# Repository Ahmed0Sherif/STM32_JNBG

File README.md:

# Intro
- This repository includes the schematics and PCB design of a double-layer STM32 development Board.
- The code name "JNBG" is in the honour of my group who helped and encouraged me in this project.
- The design is done on KiCAD 6.0
# Components List:
|Component|Description|Quantity| Was Used|
|----|-----|-------|-------|
|STM32f030f4p6|ARM® Cortex®-M0 48MHz FLASH 2.4V ~ 3.6V 32-Bit TSSOP-20 ST Microelectronics|1|Yes|
|AMS1117- 3V3| 3V3 LDO Linear Voltage Regulator  SOT-223-3|1|Yes|
|CH340C|IC Transceiver USB 2.0 2Mbps SOP-16|1|Yes|
|USBLC6-2SC6|ESD Protection TVS Unidirectional Dual Array SOT23-6|1|Yes|
|SMAJ5.0A|Unidirectional TVS 5.0V DO-214AC|1|Not Available|
|Crystal Oscillator|Crystal Oscillator 32MHz 3225|1|Yes|
|LEDs|Green and Red LEDs 0805|1* Green, 1*Red|Yes|
|Ferrite Bead|100Ω @ 100MHz 2.5A 1 100mΩ 0805|1|Yes|
|22uF Capacitor|SMD 22uF 0805|2|Replaced with 1205 Counterpart|
|4.7uF Capacitor|SMD 4.7uF 0603|2|Yes|
|1uF Capacitor|SMD 1uF 0603|2|Yes|
|100n Capacitor|SMD 100nF 0603|1|Yes|
|47nF Capacitor|SMD 47nF 0805|1|Yes|
|10nF Capacitor|SMD 10nF 0603|1|Yes|
|10pF Capacitor|SMD 10pF 0603|2|Yes|
|10k ohm Resistor|SMD 10k 0603|3|Yes|
|1k ohm Resistor|SMD 1k 0603|1|Yes|
|1k5 ohm Resistor|SMD 1k5 0603|3|Yes|
|Tactile Push Button|Micro Push button Switch 2P 3x4x2mm|1|Yes|
|PCB TH SPDT Toggle Switch| Through Hole SPDT Swithc pitch = 2.54mm |1|Yes|
|USB Port|SMD USB-B-Micro |1|Yes|
|Female Headers|TH Female Headers Vertical pitch = 2.54mm|13|Yes|
# Schematics:
## A-Power Module:

<br> - In this circuit, the AMS1117 is used to regulate 5V from USB to 3.3V, with a unidirectional TVS to protect against surges.

## B-USB Interface:

<br> - The board is provided with a USB-B Micro port, providing power and communication to the controller. 
<br> - The differential pair is connected to au nidirectional Dual TVS for ESD protection. Finally, the differentials are connected to a USB-to-TTL interface: CH340C. This variant was chosen because it can operate without an external crystal.
<br> - It is worth mentioning that until this time, this module has not been tested yet.

## C-Main Controller:

### a- Crystal Oscillator
- For calculting the value of capacitors, the following equation is used:
<br>   Capacitor Value =  ( Load Capaitance of Crystal [10pf] + Stray Capacitance of PCB [maximum estimate = 10pF] ) / 2
- Source: Phill's Lab Course on KiCAD 6.0
### b- Power:
- According to the datasheet of STM32f03x, it is recommeded to connect VDD pin to the shown capacitances.
- For more stable ADC performance, a ferrite bead is added to the VDDA connections.
### c- Interfacing:
- GPIO pins are connected to headers for easier interface, while taking speical signals into considerations (i.e. I2C pair)
- A SPDT switch is added to control the BOOT0 pin, and a RST button is added.
- For experimental purposes, extra pair of headers are added to power the STM32 directly, bypassing the regulator.

# PCB View:

# Final Result:

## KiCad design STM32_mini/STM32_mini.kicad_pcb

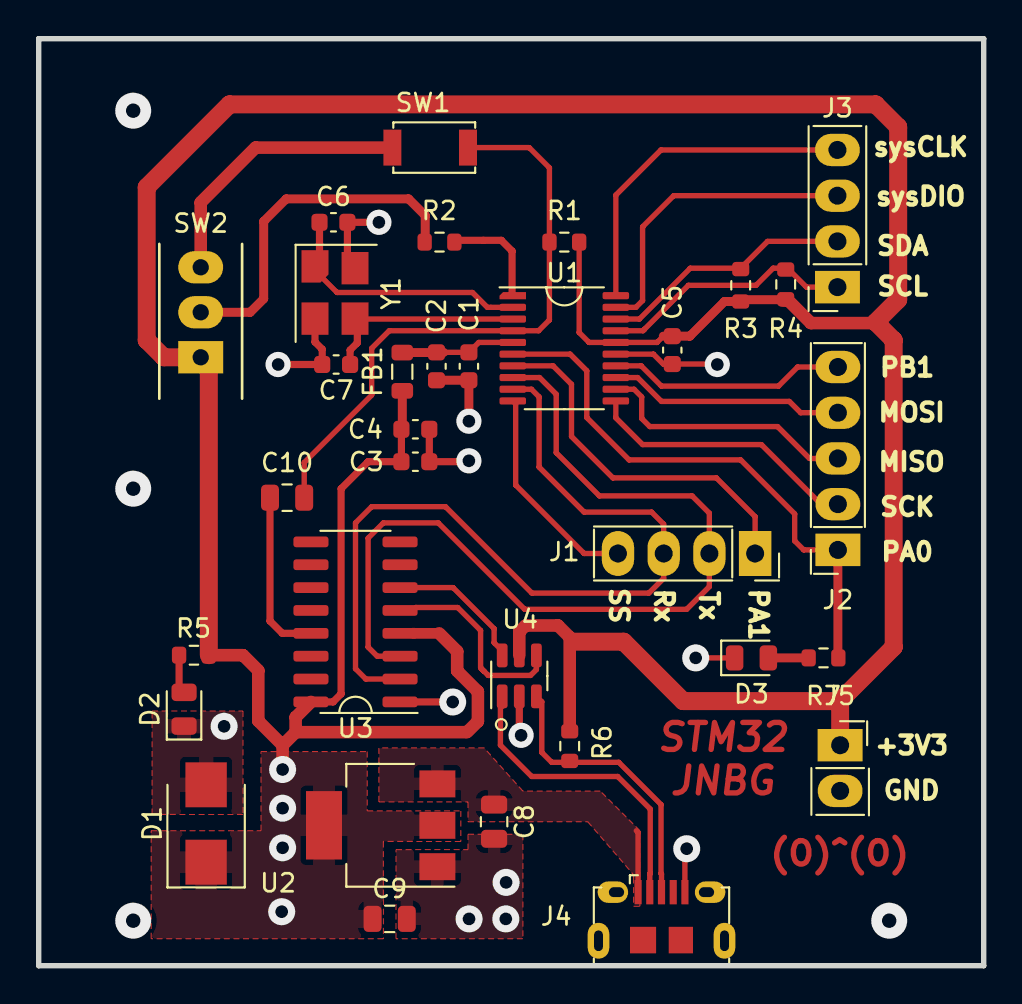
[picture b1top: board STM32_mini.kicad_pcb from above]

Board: 2 copper layers, 52.5 x 51.5 mm, 33 parts (0 on the bottom side), 29 nets.

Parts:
C1: 10n; C_0603_1608Metric
C2, C3: 1u; C_0603_1608Metric
C4: 4.7u; C_0603_1608Metric
C5: 100n; C_0603_1608Metric
C6, C7: 10p; C_0603_1608Metric
C8, C9: 22u; C_0805_2012Metric
C10: 47n; C_0805_2012Metric
D1: SMAJ5.0A; D_SMB
D2, D3: LED; LED_0805_2012Metric
FB1: 100R; L_0805_2012Metric
J1, J3: Conn_01x04_Female; PinSocket_1x04_P2.54mm_Vertical
J2: Conn_01x05_Female; PinSocket_1x05_P2.54mm_Vertical
J4: USB_B_Micro; USB_Micro-B_Amphenol_10118194_Horizontal
J5: Conn_01x02_Female; PinSocket_1x02_P2.54mm_Vertical
R1, R3, R4: 10k; R_0603_1608Metric
R2: 1k; R_0603_1608Metric
R5, R6, R7: 1k5; R_0603_1608Metric
SW1: SW_Push; SW_SPST_B3U-1000P
SW2: SW_SPDT; SW_CuK_OS102011MA1QN1_SPDT_Angled
U1: STM32F030F4Px; TSSOP-20_4.4x6.5mm_P0.65mm
U2: AMS1117-3.3; SOT-223-3_TabPin2
U3: CH340C; SOIC-16_3.9x9.9mm_P1.27mm
U4: USBLC6-2SC6; SOT-23-6
Y1: 32MHz; Crystal_SMD_3225-4Pin_3.2x2.5mm_HandSoldering

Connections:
+3.3VA: C1.1, C2.1, FB1.1, U1.5 (VDDA)
+3V3: C3.1, C4.1, C5.1, C9.1, D1.1 (A1), FB1.2, J5.1, R1.1, R3.1, R4.1, R5.1, R6.1, SW2.1 (A), U1.16 (VDD), U2.2 (VO), U3.4 (V3), U3.16 (VCC), U4.5 (VBUS)
/CH_D+: U3.5 (UD+), U4.4 (I/O2)
/CH_D-: U3.6 (UD-), U4.6 (I/O1)
/DTR: C10.2, U3.13 (~DTR)
/I2C_SCL: J3.1, R4.2, U1.17 (PA9)
/I2C_SDA: J3.2, R3.2, U1.18 (PA10)
/MISO: J2.3, U1.12 (PA6)
/MOSI: J2.4, U1.13 (PA7)
/NRST: C10.1, R1.2, SW1.2, U1.4 (NRST)
/RX: J1.3, U1.9 (PA3), U3.2 (TXD)
/SCK: J2.2, U1.11 (PA5)
/SS: J1.4, U1.10 (PA4)
/SYS_SWCLK: J3.4, U1.20 (PA14)
/SYS_SWDIO: J3.3, U1.19 (PA13)
/TX: J1.2, U1.8 (PA2), U3.3 (RXD)
/USB_D+: J4.3 (D+), R6.2, U4.3 (I/O2)
/USB_D-: J4.2 (D-), U4.1 (I/O1)
GND: C1.2, C2.2, C3.2, C4.2, C5.2, C6.2, C7.2, C8.2, C9.2, D1.2 (A2), D2.1 (K), D3.1 (K), J4.5 (GND), J5.2, SW1.1, SW2.3 (C), U1.15 (VSS), U2.1 (GND), U3.1 (GND), U4.2 (GND), Y1.2, Y1.4
unnamed: C6.1, U1.2 (PF0), Y1.1
unnamed: C7.1, U1.3 (PF1), Y1.3
unnamed: D2.2 (A), R5.2
unnamed: D3.2 (A), R7.2
unnamed: J1.1, U1.7 (PA1)
unnamed: J2.1, R7.1, U1.6 (PA0)
unnamed: R2.1, SW2.2 (B)
unnamed: R2.2, U1.1 (BOOT0)
PB1: J2.5, U1.14 (PB1)
VCC: C8.1, J4.1 (VBUS), U2.3 (VI)

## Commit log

2023-08-18 Added files of Project
2023-09-26 Update README.md
    Added Some info regarding the development board.
2023-09-26 Overall Design Update
2023-09-26 Added Schematics PDF
